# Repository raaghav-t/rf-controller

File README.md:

# BEAMO

BEAMO is a simple, low-cost RF remote controller for robots and toys based on the common nRF24L01+ and its more ubiquitous counterfeits. 32 may be operated in the same space by selecting different channels using the configuration DIP switch.

The board itself is a simple 2-layer PCB designed to be operated without an enclosure. There are mounting holes to allow attachment of a custom grip.

Example receiver code has been tested on an Arduino Uno using a matching nRF24L01+ module.

# Firmware

The remote is intended for real-time control of a vehicle. As such, it sends button updates at a minimum of every 100ms. When the data changes, it may send as frequently as every 10ms.

The remote firmware was built in PlatformIO (for Raspberry Pi Pico) but should also be portable to the Arduino IDE. The receiver example for Arduino Uno is built in the Arduino IDE.

# BOM

| Reference | Name | Approx Cost | Description |
| :-:       | :--  | :-: | :-- |
| RZ1 | [RP2040-Zero](https://www.aliexpress.us/item/3256804095235134.html) | $3.25 | Inexpensive RP2040-based microcontroller board |
| J1 | [nRF24L01+ module](https://www.amazon.com/gp/product/B082VLTTTX) | $2.60/pair | RF module (affixed with [2x4 0.1" connector](https://www.amazon.com/dp/B01IHBCO2K)) |
| SW1-4, SW6-8 | [TS02-66-50-BK-100-SCR-D](https://www.digikey.com/en/products/detail/cui-devices/TS02-66-50-BK-100-SCR-D/15634357)| $0.56 per 7 | Pushbuttons (low-force) |
| SW10 | [DS04-254-1L-05BK](https://www.digikey.com/en/products/detail/cui-devices/DS04-254-1L-05BK/11310878) | $0.64 | 5-position DIP switch |
| SW5 | [PS4 controller joystick](https://www.amazon.com/dp/B09WDNSBBR) | $1.30 | Generic PS4 joystick (ALPS TKJXV1224-like) |
| SW9 | [0.1" SPDT switch](https://www.amazon.com/dp/B09R43HCY3) | $0.10 | Slide switch (for power) |
| BT1 | [2xAA battery holder](https://www.amazon.com/dp/B013GNC08C) | $0.75 | Battery holder (held on with double-sided tape) |

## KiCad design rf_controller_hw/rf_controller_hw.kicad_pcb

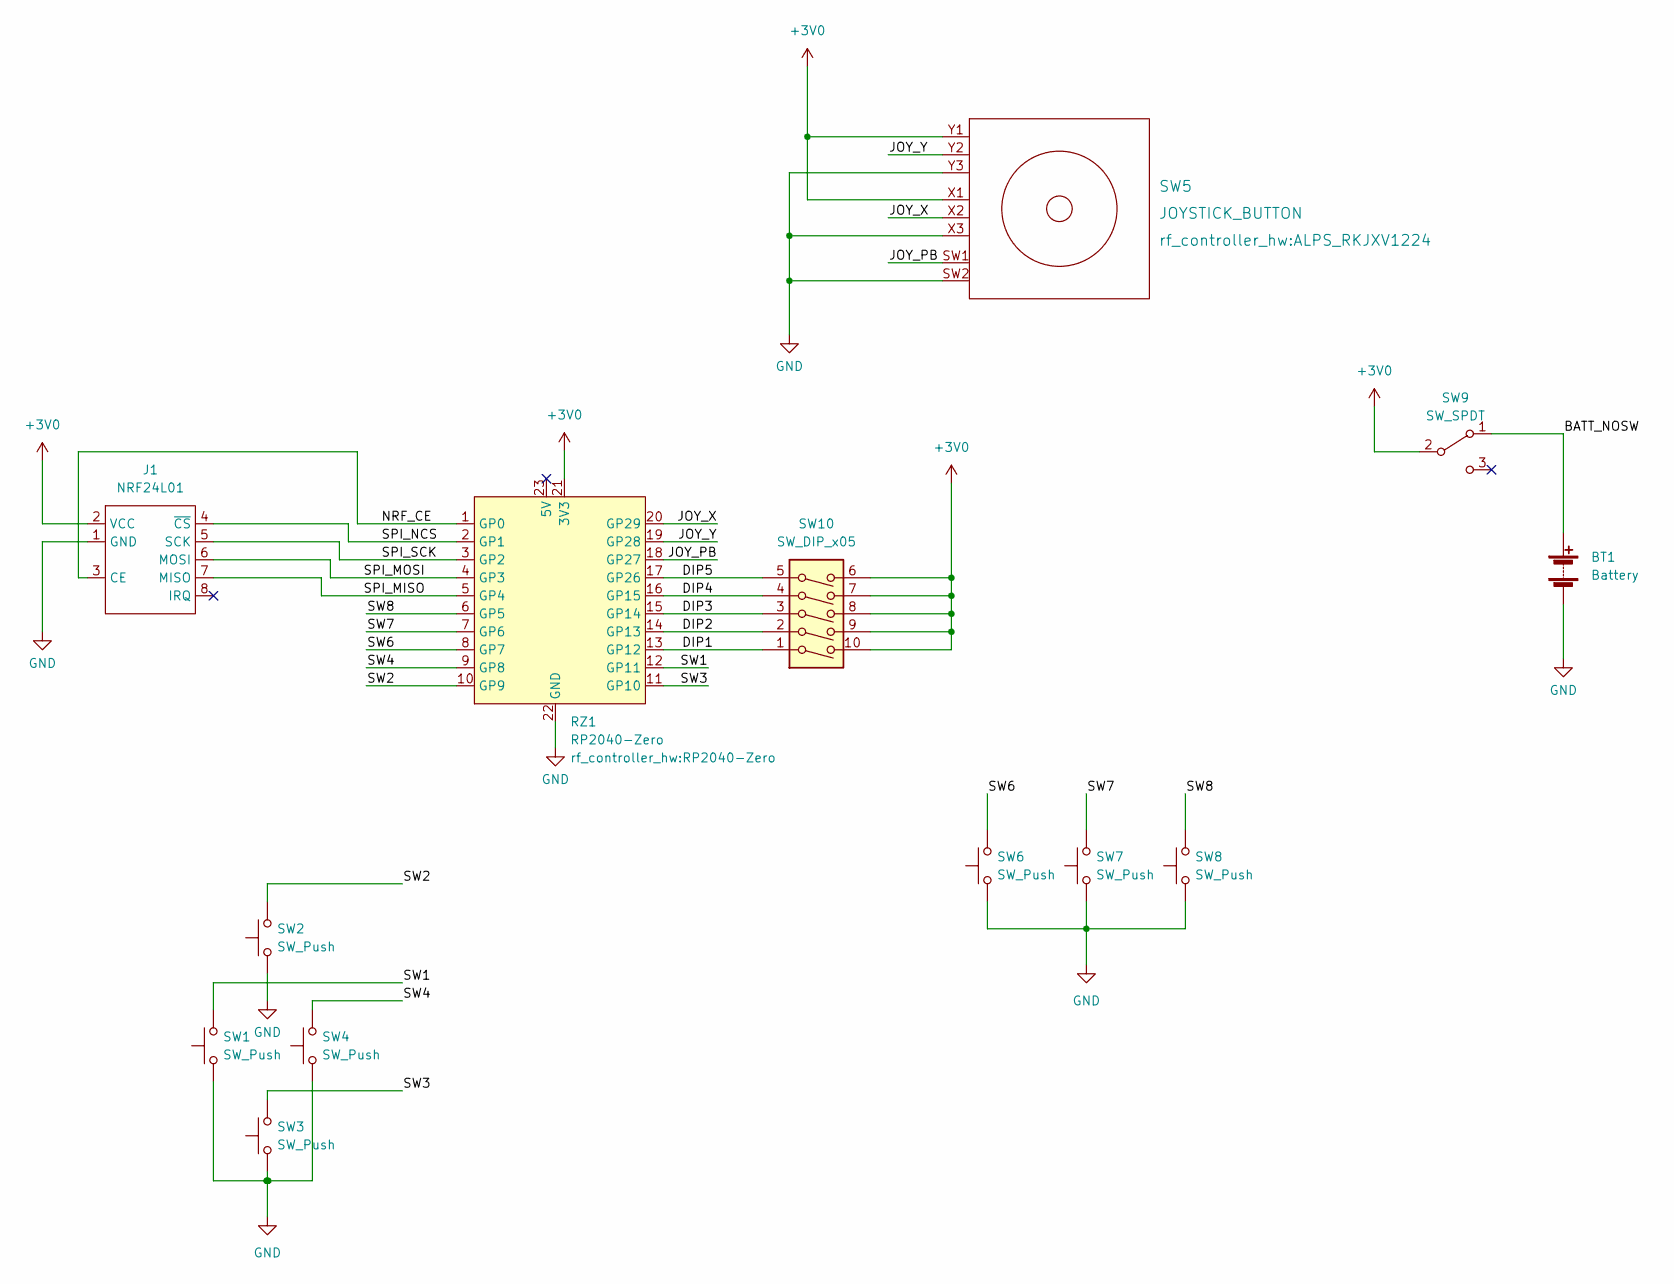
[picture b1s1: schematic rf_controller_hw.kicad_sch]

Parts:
BT1: Battery; 2AA_BATTERY
J1: NRF24L01; NRF24L01+
RZ1: RP2040-Zero
SW1, SW2, SW3, SW4, SW6, SW7, SW8: SW_Push; SW_PUSH_6mm_H5mm
SW5: JOYSTICK_BUTTON; ALPS_RKJXV1224
SW9: SW_SPDT; PinHeader_1x03_P2.54mm_Vertical
SW10: SW_DIP_x05; SW_DIP_SPSTx05_Slide_9.78x14.88mm_W7.62mm_P2.54mm

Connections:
+3V0: J1.2 (VCC), RZ1.21 (3V3), SW5.X1, SW5.Y1, SW9.2 (B), SW10.6, SW10.7, SW10.8, SW10.9, SW10.10
/BATT_NOSW: BT1.1 (+), SW9.1 (A)
/DIP1: RZ1.13 (GP12), SW10.1
/DIP2: RZ1.14 (GP13), SW10.2
/DIP3: RZ1.15 (GP14), SW10.3
/DIP4: RZ1.16 (GP15), SW10.4
/DIP5: RZ1.17 (GP26), SW10.5
/JOY_PB: RZ1.18 (GP27), SW5.SW1
/JOY_X: RZ1.20 (GP29), SW5.X2
/JOY_Y: RZ1.19 (GP28), SW5.Y2
/NRF_CE: J1.3 (CE), RZ1.1 (GP0)
/SPI_MISO: J1.7 (MISO), RZ1.5 (GP4)
/SPI_MOSI: J1.6 (MOSI), RZ1.4 (GP3)
/SPI_NCS: J1.4 (~CS), RZ1.2 (GP1)
/SPI_SCK: J1.5 (SCK), RZ1.3 (GP2)
/SW1: RZ1.12 (GP11), SW1.2
/SW2: RZ1.10 (GP9), SW2.2
/SW3: RZ1.11 (GP10), SW3.2
/SW4: RZ1.9 (GP8), SW4.2
/SW6: RZ1.8 (GP7), SW6.2
/SW7: RZ1.7 (GP6), SW7.2
/SW8: RZ1.6 (GP5), SW8.2
GND: BT1.2 (-), J1.1 (GND), RZ1.22 (GND), SW1.1, SW2.1, SW3.1, SW4.1, SW5.SW2, SW5.X3, SW5.Y3, SW6.1, SW7.1, SW8.1

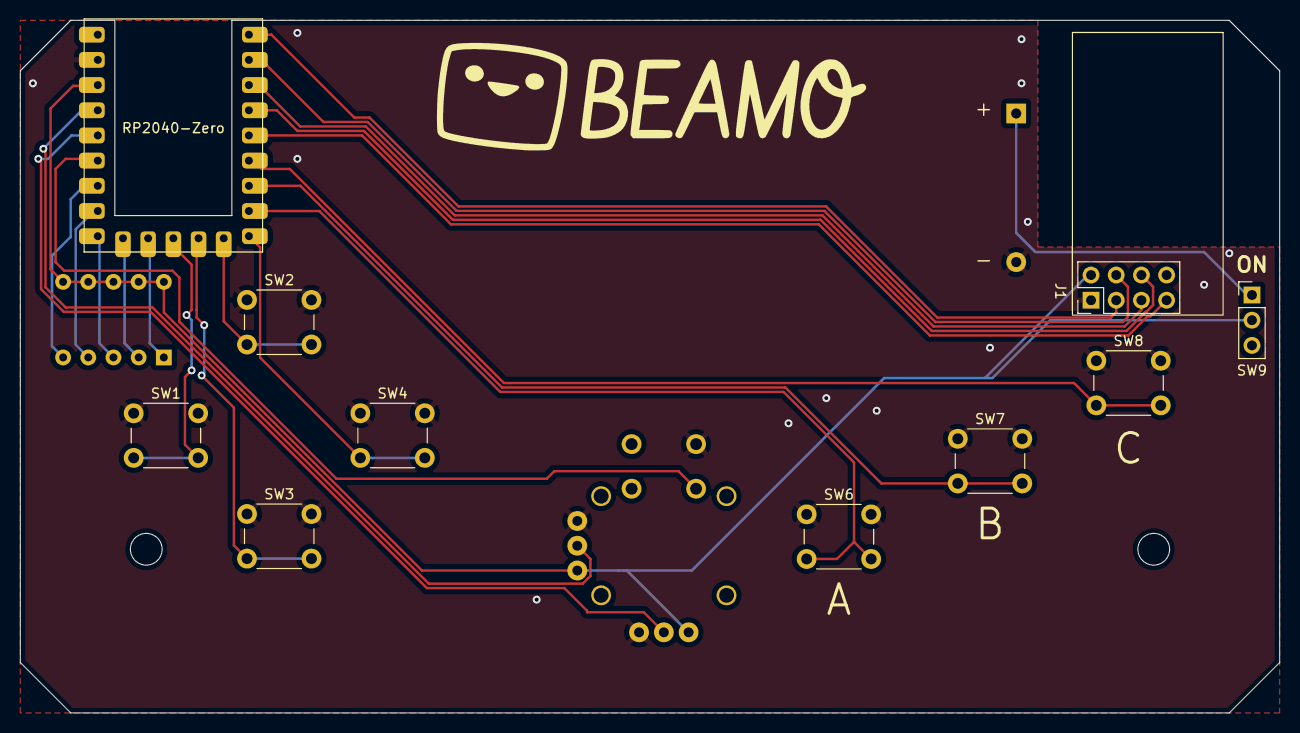
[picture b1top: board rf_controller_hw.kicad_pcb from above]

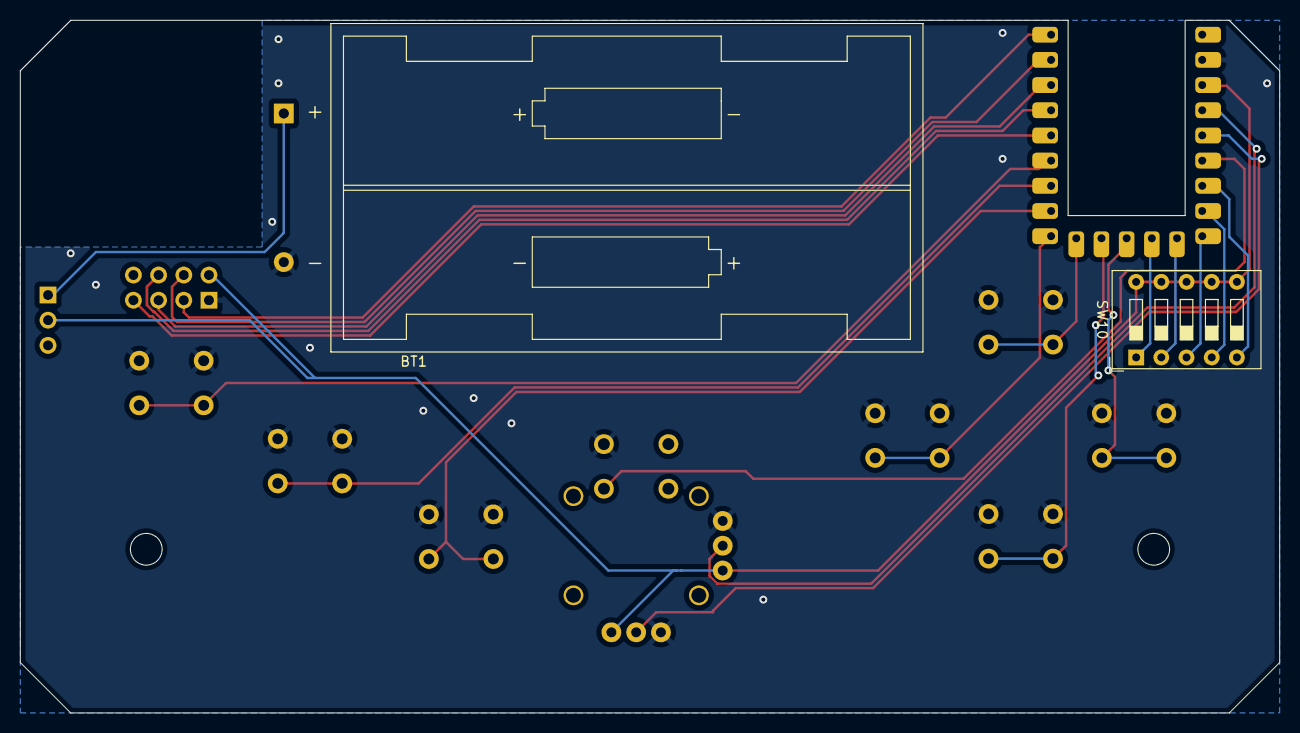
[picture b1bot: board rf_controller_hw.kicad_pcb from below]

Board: 2 copper layers, 127.0 x 69.8 mm, 13 parts (2 on the bottom side), 23 nets.

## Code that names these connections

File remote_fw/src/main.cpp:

/* 
 * This file is part of the rf-controller (https://github.com/bnahill/rf-controller).
 * Copyright (c) 2022 Ben Nahill.
 * 
 * This program is free software: you can redistribute it and/or modify  
 * it under the terms of the GNU General Public License as published by  
 * the Free Software Foundation, version 3.
 *
 * This program is distributed in the hope that it will be useful, but 
 * WITHOUT ANY WARRANTY; without even the implied warranty of 
 * MERCHANTABILITY or FITNESS FOR A PARTICULAR PURPOSE. See the GNU 
 * General Public License for more details.
 *
 * You should have received a copy of the GNU General Public License 
 * along with this program. If not, see <http://www.gnu.org/licenses/>.
 */

#include <Arduino.h>
#include <SPI.h>
#include <RF24.h>
#include <RF24_config.h>
#include <Adafruit_NeoPixel.h>


static constexpr uint8_t PIN_NRF_CE = 0;
static constexpr uint8_t PIN_NRF_NCS = 1;
static constexpr uint8_t PIN_NRF_SCK = 2;
static constexpr uint8_t PIN_NRF_COPI = 3;
static constexpr uint8_t PIN_NRF_CIPO = 4;

static constexpr uint8_t PIN_SW_UP = 9;
static constexpr uint8_t PIN_SW_DOWN = 10;
static constexpr uint8_t PIN_SW_LEFT = 11;
static constexpr uint8_t PIN_SW_RIGHT = 8;

static constexpr uint8_t PIN_SW_A = 7;
static constexpr uint8_t PIN_SW_B = 6;
static constexpr uint8_t PIN_SW_C = 5;

static constexpr uint8_t PIN_JOYX = 28;
static constexpr uint8_t PIN_JOYY = 29;
static constexpr uint8_t PIN_JOY_PUSH = 27;

static constexpr uint8_t PIN_CONF5 = 26;
static constexpr uint8_t PIN_CONF4 = 15;
static constexpr uint8_t PIN_CONF3 = 14;
static constexpr uint8_t PIN_CONF2 = 13;
static constexpr uint8_t PIN_CONF1 = 12;

static constexpr uint8_t PIN_RGBLED = 16;

// Single RGB LED
Adafruit_NeoPixel strip(1, PIN_RGBLED, NEO_GRB + NEO_KHZ800);

// Compact structure to convey the current input state
typedef struct {
  uint16_t joy_x; //!< Joystick X-axis range 0 (left) - 4095 (right)
  uint16_t joy_y; //!< Joystick Y-axis range 0 (down) - 4095 (up)
  uint8_t up: 1;
  uint8_t down: 1;
  uint8_t left: 1;
  uint8_t right: 1;
  uint8_t a: 1;
  uint8_t b: 1;
  uint8_t c: 1;
  uint8_t joy_push: 1;
} __attribute__((packed)) button_status_t;

static_assert(sizeof(button_status_t) == 5, "button_status_t should be 5B");

// This address can be anything as long as it matches on the receiver side
uint8_t const NRF_ADDRESS[6] = "00001";
RF24 radio(PIN_NRF_CE, PIN_NRF_NCS);

/**
 * @brief Read button input
 * 
 * @return button_status_t 
 */
static button_status_t read_buttons(){
  button_status_t stat = {0};
  
  stat.joy_x = analogRead(PIN_JOYX);
  stat.joy_y = 4096 - analogRead(PIN_JOYY);
  stat.up = 1 - digitalRead(PIN_SW_UP);
  stat.down = 1 - digitalRead(PIN_SW_DOWN);
  stat.left = 1 - digitalRead(PIN_SW_LEFT);
  stat.right = 1 - digitalRead(PIN_SW_RIGHT);
  stat.a = 1 - digitalRead(PIN_SW_A);
  stat.b = 1 - digitalRead(PIN_SW_B);
  stat.c = 1 - digitalRead(PIN_SW_C);
  stat.joy_push = 1 - digitalRead(PIN_JOY_PUSH);
  return stat;
}

static constexpr bool SILENT = true;

/**
 * @brief Compare two inputs of type button_status_t
 * 
 * @param a 
 * @param b 
 * @return true If equal (with analog inputs within some threshold)
 * @return false If not equal
 */
bool status_equal(button_status_t const &a, button_status_t const &b){
  if(a.up != b.up || a.down != b.down || a.left != b.left || a.right != b.right ||
     a.a != b.a || a.b != b.b || a.c != b.c || a.joy_push != b.joy_push){
    return false;
  }
  int32_t const THRESHOLD = 15;
  if(abs((int32_t)a.joy_x - (int32_t)b.joy_x) > THRESHOLD){
    return false;
  }

  if(abs((int32_t)a.joy_y - (int32_t)b.joy_y) > THRESHOLD){
    return false;
  }
  return true;
}

button_status_t last_status = {0};

void setup() {
  if(!SILENT) Serial.begin(9600);

  // Configure the SPI pins to do SPI
  gpio_set_function(PIN_NRF_COPI, GPIO_FUNC_SPI);
  gpio_set_function(PIN_NRF_CIPO, GPIO_FUNC_SPI);
  gpio_set_function(PIN_NRF_SCK, GPIO_FUNC_SPI);

  pinMode(PIN_SW_UP, INPUT_PULLUP);
  pinMode(PIN_SW_DOWN, INPUT_PULLUP);
  pinMode(PIN_SW_LEFT, INPUT_PULLUP);
  pinMode(PIN_SW_RIGHT, INPUT_PULLUP);
  pinMode(PIN_SW_A, INPUT_PULLUP);
  pinMode(PIN_SW_B, INPUT_PULLUP);
  pinMode(PIN_SW_C, INPUT_PULLUP);
  pinMode(PIN_JOYX, INPUT);
  pinMode(PIN_JOYY, INPUT);
  pinMode(PIN_JOY_PUSH, INPUT_PULLUP);

  pinMode(PIN_CONF1, INPUT_PULLDOWN);
  pinMode(PIN_CONF2, INPUT_PULLDOWN);
  pinMode(PIN_CONF3, INPUT_PULLDOWN);
  pinMode(PIN_CONF4, INPUT_PULLDOWN);
  pinMode(PIN_CONF5, INPUT_PULLDOWN);

  analogReadResolution(12);

  delay(1000);

  if (!radio.begin()) {
    if(!SILENT) Serial.println(F("radio hardware is not responding!!"));

    strip.begin();
    strip.setBrightness(50);
    strip.show();
    // Flash red/green if the radio fails to initialize
    for(uint32_t i = 0; i < 40u; i++){
      strip.setPixelColor(0, strip.Color(0, 255, 0));
      strip.show();
      delay(50);
      strip.setPixelColor(0, strip.Color(255, 0, 0));
      strip.show();
      delay(50);
    }
    strip.setPixelColor(0, strip.Color(0, 0, 0));
    strip.show();
    while (1) {}  // hold in infinite loop
  }
  char buffer[64] = {0};
  if(!SILENT){
    snprintf(buffer, sizeof(buffer), "radio hardware initialized %u!!", radio.getChannel());
    Serial.println(buffer);
  }

  uint32_t channel = (digitalRead(PIN_CONF5) << 4) | (digitalRead(PIN_CONF4) << 3) |
                     (digitalRead(PIN_CONF3) << 2) | (digitalRead(PIN_CONF2) << 1) |
                     (digitalRead(PIN_CONF1) << 0);
  
  radio.setChannel(channel);
  if(!SILENT){
    snprintf(buffer, sizeof(buffer), "New channel %u!!", radio.getChannel());
    Serial.println(buffer);
  }
  radio.setPALevel(RF24_PA_LOW);
  radio.openWritingPipe(NRF_ADDRESS);
  radio.stopListening();

  strip.begin();
  strip.setBrightness(50);
  strip.show();

  for(uint32_t i = 0; i < 5u; i++){
    strip.setPixelColor(0, strip.Color(255, 255, 0));
    strip.show();
    delay(50);
    strip.setPixelColor(0, strip.Color(0, 0, 0));
    strip.show();
    delay(50);
  }

  last_status = read_buttons();
}

static constexpr uint32_t SAMPLE_DELAY_MS = 10u;
static constexpr uint32_t MIN_UPDATE_RATE_MS = 100u;
static constexpr uint32_t LED_TIMEOUT_MS = 1000u;
static constexpr uint32_t IDLE_TIMEOUT_MS = 5u * 60u * 1000u;

static uint32_t last_change_ms = 0u;
static uint32_t last_update_ms = 0u;

void loop() {
  // put your main code here, to run repeatedly:
  delay(SAMPLE_DELAY_MS);
  //Serial.println("Line");
  char buffer[128] = {0};
  button_status_t const status = read_buttons();
  if(!status_equal(status, last_status)){
    if(!SILENT){
      snprintf(buffer, sizeof(buffer), "Joy X %u, Y %u, PB %lu!!", status.joy_x, status.joy_y, (uint32_t)status.joy_push);
      Serial.println(buffer);

      snprintf(buffer, sizeof(buffer), "%u %u %u %u %u %u %u",
              status.up, status.down, status.left, status.right,
              status.a, status.b, status.c);
      Serial.println(buffer);
    }
    strip.setPixelColor(0, strip.Color(status.joy_x / 16, status.joy_y / 16, 0));
    strip.show();
    radio.write(&status, sizeof(button_status_t));

    last_change_ms = millis();
    last_update_ms = last_change_ms;
  } else if ( millis() - last_change_ms > MIN_UPDATE_RATE_MS ) {
    radio.write(&status, sizeof(button_status_t));
    last_update_ms = millis();
  }

  if ( millis() - last_change_ms > LED_TIMEOUT_MS ) {
    strip.setPixelColor(0, strip.Color(0, 0, 0));
    strip.show();
  }

  if ( millis() - last_change_ms > IDLE_TIMEOUT_MS ) {
    //sleep_goto_dormant_until_edge_high(10);
  }

  last_status = status;

}

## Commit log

2022-11-19 Initial hardware design commit
2022-11-24 Changed to mechanical keyboard switches
2022-11-28 Finished first draft:
    - Spread out buttons on right
    - Added power switch
    - Added a budget logo
    - Added gerbers for PCB order
2022-12-07 Fixed a bug in the first board:
    Fixed bug in RP2040-Zero pinout
    Added better logo
    Re-added mounting holes
    Switched to smaller joystick
2022-12-24 Added first cut of firmware
2022-12-24 Licenses added for each subproject
2022-12-25 Cleanup of software and unused submodule
2023-01-09 Code neatness
2023-02-06 Updated sketch movement for me127 driving robot
